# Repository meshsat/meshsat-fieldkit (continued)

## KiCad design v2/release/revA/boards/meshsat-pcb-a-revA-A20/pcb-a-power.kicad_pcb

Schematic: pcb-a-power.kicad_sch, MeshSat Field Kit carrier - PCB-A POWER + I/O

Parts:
C7, C14, C61, C62, C106: 10u; C_0805_2012Metric
C13, C44, C67, C68, C77, C90, C100, C104, C105, C107, C108: 100n; C_0603_1608Metric
C15, C42, C43, C45, C46, C47, C48, C49, C70, C75, C76, C78, C79, C80, C81, C82, C83, C88, C89, C91, C92, C93, C94, C101: 22u 10V X7R 1210; C_1210_3225Metric
C38, C71, C84: 100n 25V; C_0603_1608Metric
C39, C72, C85: 2.2u; C_0603_1608Metric
C40, C73, C86: 3.3n; C_0603_1608Metric
C41, C74, C87: 27p; C_0603_1608Metric
C50, C95, C96, C97: 100u 10V; C_1206_3216Metric
C51, C52, C53, C54, C55, C56, C57, C58, C59, C60: 10u 25V 1210; C_1210_3225Metric
C63, C64: 47n; C_0603_1608Metric
C65: 4.7u; C_0805_2012Metric
C66: 1n; C_0603_1608Metric
C69, C98: 1u; C_0603_1608Metric
C99: 10n; C_0603_1608Metric
D2: SMBJ5.0A; D_SMB
F2, F3, F4: 10 A mini blade (Keystone 3568 holder): pack node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; Fuseholder_Blade_Mini_Keystone_3568
F5: 15 A mini blade (Keystone 3568 holder): pack node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; Fuseholder_Blade_Mini_Keystone_3568
F6: 2.5A hold 30V 1812; Fuse_1812_4532Metric
J_5V_M1: rail M1 to PCB-B J_5V_M1 (JST-VH, 18 AWG): + -; JST_VH_B2P-VH_1x02_P3.96mm_Vertical
J_5V_M2: rail M2 to PCB-B J_5V_M2 (JST-VH, 18 AWG): + -; JST_VH_B2P-VH_1x02_P3.96mm_Vertical
J_5V_PI: Pi rail 5.1 V 5 A to PCB-B J_5V_PI (JST-VH, 18 AW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; JST_VH_B2P-VH_1x02_P3.96mm_Vertical
J_AB1: A-B interconnect (IDC 2x9, top side); IDC-Header_2x09_P2.54mm_Vertical
J_BM1, J_BM2, J_BM3, J_BM4, J_BM5, J_BM6, J_BM7: SMP-MAX slide-on receptacle R222M00720 (underside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; Radiall_SMPMAX_R222M00720
J_CN1, J_CN2, J_CN3, J_CN4: 9 A spring pin, module return CELL_N (Mill-Max 08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; Mill-Max_0858_power_pin
J_CP1, J_CP2, J_CP3, J_CP4: 9 A spring pin, CELL+ (Mill-Max 0858 class, dock 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; Mill-Max_0858_power_pin
J_DOCK: spring pins to the dock block (2x6, Preci-Dip 813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; PogoPins_2x6
J_HEAT: 12 V heating pad on the battery module (XH2.5): +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; JST_XH_B2B-XH-A_1x02_P2.50mm_Vertical
J_LEDS1: front-wall LED row (XH2.5): PWR MESH SAT LTE SYS; JST_XH_B10B-XH-A_1x10_P2.50mm_Vertical
J_MAINSW: MAIN button lead from the panel (XH2.5): PB, GND; JST_XH_B2B-XH-A_1x02_P2.50mm_Vertical
J_MEZZ1: APRS mezzanine harness (IDC 2x8): I2S and I2C for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; IDC-Header_2x08_P2.54mm_Vertical
J_MEZZ_PWR1: mezzanine 8 V boost feed (JST-VH): cell node thro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; JST_VH_B2P-VH_1x02_P3.96mm_Vertical
J_PRE1: pre-charge pin, longer, mates first (32.24 AX); Mill-Max_0858_power_pin
J_RF1, J_RF2, J_RF3, J_RF4, J_RF5, J_RF6, J_RF7: SMA jack (Amphenol 132134, vertical), pigtail fro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; SMA_Amphenol_132134-11_Vertical
J_WALL1: USB-A receptacle, internal cable to the Glenair 2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; USB_A_Stewart_SS-52100-001_Horizontal
L2, L3, L4: 2.2uH XAL1010-222MED (Isat 34 A, 10 mm); L_Coilcraft_XAL1010-XXX
L5: 2.2uH XAL4030-222MEB (Isat 7.4 A) between SW1 and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; L_Coilcraft_XAL4030-XXX
L6: 3.3uH XAL4020-332MEB; L_Coilcraft_XAL4020-XXX
Q5: 2N7002: Pi GPIO high = pull KILL low = power off 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; SOT-23
R18: 1k; R_0603_1608Metric
R34, R59, R60, R72, R76: 10k; R_0603_1608Metric
R35, R36, R37, R38: 330R; R_0603_1608Metric
R39, R58, R67, R68, R69, R70, R73, R77: 100k; R_0603_1608Metric
R44, R61, R64: 8.87k; R_0603_1608Metric
R47, R62: 102k 1%; R_0603_1608Metric
R48, R63: 13.7k 1%; R_0603_1608Metric
R51: 10R 2W 2512; R_2512_6332Metric
R52: 3 mOhm 1% 3 W 2512 shunt (RALEC LR2512-23R003F4):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; R_2512_6332Metric; LCSC C154688
R53: 4.7k 1% (PROG: 1S, 750 kHz); R_0603_1608Metric
R54: 16.5k 1%; R_0603_1608Metric
R55: 34.8k 1%; R_0603_1608Metric
R56: 5.23k 1% (RT1 JEITA); R_0603_1608Metric
R57: 30.1k 1% (RT2 JEITA); R_0603_1608Metric
R65: 75k 1%; R_0603_1608Metric
R66, R75: 10k 1%; R_0603_1608Metric
R71: 1.02k 1% (2.0 A); R_0603_1608Metric
R74: 33.2k 1%; R_0603_1608Metric
R78: 0.1R 1% 1206; R_1206_3216Metric
RT1: 10k NTC 0603 1% (gauge temperature, beside the do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; R_0603_1608Metric
TP1: +5V_M1; TestPoint_Pad_D1.5mm
TP2: GND; TestPoint_Pad_D1.5mm
TP3: +3V3; TestPoint_Pad_D1.5mm
TP4: CELL_N; TestPoint_Pad_D1.5mm
TP5: CELL+; TestPoint_Pad_D1.5mm
TP6: SHORE_INHIBIT; TestPoint_Pad_D1.5mm
TP7: GAUGE_ALERT; TestPoint_Pad_D1.5mm
TP8: I2S_DIN; TestPoint_Pad_D1.5mm
TP9: TX_INHIBIT_n; TestPoint_Pad_D1.5mm
TP10: SHORE_12V; TestPoint_Pad_D1.5mm
TP11: CHG_INT; TestPoint_Pad_D1.5mm
TP12: +5V_M2; TestPoint_Pad_D1.5mm
TP13: +5V_PI; TestPoint_Pad_D1.5mm
TP14: DOCK_SPARE; TestPoint_Pad_D1.5mm
TP15: BOOST_EN; TestPoint_Pad_D1.5mm
TP16: CELL_SENSE_P; TestPoint_Pad_D1.5mm
TP17: EXP_SP2; TestPoint_Pad_D1.5mm
TP18: EXP_SP3; TestPoint_Pad_D1.5mm
TP19: EXP2_SP0; TestPoint_Pad_D1.5mm
TP20: EXP2_SP1; TestPoint_Pad_D1.5mm
TP21: EXP2_SP2; TestPoint_Pad_D1.5mm
TP22: EXP2_SP3; TestPoint_Pad_D1.5mm
TP23: EXP2_SP4; TestPoint_Pad_D1.5mm
TP24: EXP2_SP5; TestPoint_Pad_D1.5mm
TP25: EXP2_SP6; TestPoint_Pad_D1.5mm
TP26: EXP2_SP7; TestPoint_Pad_D1.5mm
TP27: EXP2_SP8; TestPoint_Pad_D1.5mm
TP29: EXP_SP4; TestPoint_Pad_D1.5mm
TP30: EXP_SP5; TestPoint_Pad_D1.5mm
TP31: EXP_SP6; TestPoint_Pad_D1.5mm
TP32: EXP_SP7; TestPoint_Pad_D1.5mm
TP33: EXP_SP8; TestPoint_Pad_D1.5mm
TP34: EXP_SP9; TestPoint_Pad_D1.5mm
TP35: EXP_SP10; TestPoint_Pad_D1.5mm
TP36: EXP_SP11; TestPoint_Pad_D1.5mm
U5: TPS563201 3.3 V buck from M1; SOT-23-6
U19: PCA9555PW (0x21); TSSOP-24_4.4x7.8mm_P0.65mm; LCSC C5626
U20: BQ25792 1S charger from SHORE_12V (3 A set over I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; Texas_RQM0029A_QFN-29_4x4mm; LCSC C2862876
U21: BQ34Z100-G1 gauge (I2C 0x55, SCALED for 42 Ah, 3 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; TSSOP-14_4.4x5mm_P0.65mm; LCSC C91302
U22: TPS61288L boost +5V_M1 (15 A switch, 500 kHz, no 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; Texas_RQQ0011A_VQFN-HR-11_2.5x3mm; LCSC C7498841
U23: TPS61288L boost +5V_M2 (15 A switch, 500 kHz, no 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; Texas_RQQ0011A_VQFN-HR-11_2.5x3mm; LCSC C7498841
U24: TPS61288L boost +5V_PI (15 A switch, 500 kHz, no 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; Texas_RQQ0011A_VQFN-HR-11_2.5x3mm; LCSC C7498841
U25: LTC2954CTS8-1 push-button on/off controller; TSOT-23-8; LCSC C683782
U26: TPS259571DSGR eFuse 12 V 2.0 A for the heating pad; Texas_DSG0008A_WSON-8-1EP_2x2mm_P0.5mm_EP0.9x1.6mm; LCSC C471038
U28: TPS2065CDBV; SOT-23-5
U29: INA219AIDCN; SOT-23-8; LCSC C138024
U30: USBLC6-2SC6; SOT-23-6; LCSC C7519
U31: PCA9555PW (0x24): wall port, heating pad, charger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; TSSOP-24_4.4x7.8mm_P0.65mm; LCSC C5626

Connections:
+3V3: C15.1, C101.1, C105.1, C107.1, C108.1, J_MEZZ1.12, L6.2, R34.2, R35.1, R36.1, R37.1, R38.1, R60.2, R68.2, R72.2, R74.1, R76.2, R77.2, TP3.1, U19.21 (A0), U19.24 (VDD), U29.4 (VS), U31.3 (A2), U31.24 (VDD)
/5V_WALL: C106.1, J_WALL1.1 (VBUS), R78.2, U29.2 (IN-), U30.5 (VBUS)
/+3V3_AB: J_AB1.17, J_MEZZ1.2
/+5V_M1: C14.1, C45.1, C46.1, C47.1, C48.1, C49.1, C70.1, C95.1, C104.1, D2.1 (A1), J_5V_M1.1, R18.1, R47.1, TP1.1, U5.3 (VIN), U5.5 (EN), U22.5, U28.5 (IN)
/+5V_M2: C78.1, C79.1, C80.1, C81.1, C82.1, C83.1, C96.1, J_5V_M2.1, R62.1, TP12.1, U23.5
/+5V_PI: C91.1, C92.1, C93.1, C94.1, C97.1, J_5V_PI.1, R65.1, TP13.1, U24.5
/BOOST1_IN: C42.1, C43.1, C44.1, F3.2, L2.1, U22.7
/BOOST2_IN: C75.1, C76.1, C77.1, F4.2, L3.1, U23.7
/BOOST3_IN: C88.1, C89.1, C90.1, F5.2, L4.1, U24.7
/BOOST_EN: R67.1, TP15.1, U22.6, U23.6, U24.6, U25.6
/BST1: C38.1, U22.8
/BST2: C71.1, U23.8
/BST3: C84.1, U24.8
/BST33: C13.1, U5.6 (VBST)
/BTST1: C63.1, U20.4
/BTST2: C64.1, U20.19
/CELL+: C7.1, C50.1, C61.1, C62.1, C68.1, C98.1, F2.1, F3.1, F4.1, F5.1, J_CP1.1, J_CP2.1, J_CP3.1, J_CP4.1, R51.2, R67.2, R69.2, TP5.1, U20.22, U20.23, U21.5, U21.6, U25.1
/CELL_N: C68.2, C69.2, J_CN1.1, J_CN2.1, J_CN3.1, J_CN4.1, R52.1, TP4.1, U21.8, U21.9
/CELL_SENSE_P: C67.1, J_DOCK.11, TP16.1, U20.18, U21.4
/CHG_INT: R60.1, TP11.1, U20.21, U31.8 (IO0_4)
/CHG_STAT: R59.1, U20.1, U31.10 (IO0_6)
/COMP1: C41.1, R44.1, U22.2
/COMP1C: C40.1, R44.2
/COMP2: C74.1, R61.1, U23.2
/COMP2C: C73.1, R61.2
/COMP3: C87.1, R64.1, U24.2
/COMP3C: C86.1, R64.2
/DOCK_SPARE: J_DOCK.12, TP14.1
/EN_WALL: R77.1, U28.4 (EN), U31.4 (IO0_0)
/EXP2_SP0: TP19.1, U31.11 (IO0_7)
/EXP2_SP1: TP20.1, U31.13 (IO1_0)
/EXP2_SP2: TP21.1, U31.14 (IO1_1)
/EXP2_SP3: TP22.1, U31.15 (IO1_2)
/EXP2_SP4: TP23.1, U31.16 (IO1_3)
/EXP2_SP5: TP24.1, U31.17 (IO1_4)
/EXP2_SP6: TP25.1, U31.18 (IO1_5)
/EXP2_SP7: TP26.1, U31.19 (IO1_6)
/EXP2_SP8: TP27.1, U31.20 (IO1_7)
/EXP_INT: J_AB1.9, R34.1, U19.1 (~INT), U31.1 (~INT)
/EXP_SP2: TP17.1, U19.9 (IO0_5)
/EXP_SP3: TP18.1, U19.20 (IO1_7)
/EXP_SP4: TP29.1, U19.4 (IO0_0)
/EXP_SP5: TP30.1, U19.5 (IO0_1)
/EXP_SP6: TP31.1, U19.6 (IO0_2)
/EXP_SP7: TP32.1, U19.7 (IO0_3)
/EXP_SP8: TP33.1, U19.16 (IO1_3)
/EXP_SP9: TP34.1, U19.17 (IO1_4)
/EXP_SP10: TP35.1, U19.18 (IO1_5)
/EXP_SP11: TP36.1, U19.19 (IO1_6)
/FB1: R47.2, R48.1, U22.1
/FB2: R62.2, R63.1, U23.1
/FB3: R65.2, R66.1, U24.1
/FB33: R74.2, R75.1, U5.4 (VFB)
/FLT_WALL: R76.1, U28.3 (~FLT), U31.6 (IO0_2)
/GAUGE_ALERT: TP7.1, U21.1, U31.9 (IO0_5)
/HEAT_DVDT: C99.1, U26.1
/HEAT_EN: R73.1, U26.2, U31.5 (IO0_1)
/HEAT_FLT: R72.1, U26.6, U31.7 (IO0_3)
/HEAT_ILM: R71.1, U26.7
/HEAT_IN: C100.1, F6.2, U26.3, U26.4
/HEAT_OUT: J_HEAT.1, U26.5
/I2S_BCLK: J_AB1.11, J_MEZZ1.3
/I2S_DIN: J_AB1.16, J_MEZZ1.7, TP8.1
/I2S_DOUT: J_AB1.15, J_MEZZ1.6
/I2S_LRCLK: J_AB1.12, J_MEZZ1.4
/ILIM_HIZ: R54.2, R55.1, U20.17
/KILL: Q5.3 (D), R69.1, U25.8
/LED_LTE_A: J_LEDS1.7, R37.2
/LED_LTE_K: J_LEDS1.8, U19.14 (IO1_1)
/LED_MESH_A: J_LEDS1.3, R35.2
/LED_MESH_K: J_LEDS1.4, U19.11 (IO0_7)
/LED_PWR_A: J_LEDS1.1, R18.2
/LED_SAT_A: J_LEDS1.5, R36.2
/LED_SAT_K: J_LEDS1.6, U19.13 (IO1_0)
/LED_SYS_A: J_LEDS1.9, R38.2
/LED_SYS_K: J_LEDS1.10, U19.15 (IO1_2)
/MAIN_PB: J_MAINSW.1, U25.2
/MEZZ_CELL: F2.2, J_MEZZ_PWR1.1
/MEZZ_EN: J_MEZZ1.11, U19.10 (IO0_6)
/PI_KILL: J_AB1.2, Q5.1 (G), R70.1
/PI_SHDN_REQ: J_AB1.1, R68.1, U25.5
/PMID: C53.1, C54.1, C55.1, U20.29
/PRECHG: J_PRE1.1, R51.1
/PROG: R53.1, U20.20
/QON: R58.2, U20.12
/REG25: C69.1, RT1.1, U21.7
/REGN: C65.1, R54.1, R56.1, R58.1, R59.2, U20.5
/RF_IRIDIUM: J_BM6.1 (In), J_RF6.1 (In)
/RF_LORA: J_BM7.1 (In), J_RF7.1 (In)
/RF_LTE: J_BM5.1 (In), J_RF5.1 (In)
/RF_SDR: J_BM4.1 (In), J_RF4.1 (In)
/RF_UHF: J_BM1.1 (In), J_RF1.1 (In)
/RF_WIFI24: J_BM2.1 (In), J_RF2.1 (In)
/RF_WIFI58: J_BM3.1 (In), J_RF3.1 (In)
/SCL: J_AB1.8, J_MEZZ1.14, U19.22 (SCL), U20.14, U21.13, U29.5 (SCL), U31.22 (SCL)
/SDA: J_AB1.7, J_MEZZ1.9, U19.23 (SDA), U20.15, U21.14, U29.6 (SDA), U29.7 (A0), U29.8 (A1), U31.23 (SDA)
/SDRV: C66.1, U20.24
/SHORE_12V: C51.1, C52.1, F6.1, J_DOCK.1, J_DOCK.2, J_DOCK.3, J_DOCK.4, TP10.1, U20.2, U20.3, U20.8, U20.9
/SHORE_INHIBIT: J_DOCK.8, TP6.1, U19.8 (IO0_4)
/SW1: C38.2, L2.2, U22.4, U22.9
/SW1_CHG: C63.2, L5.1, U20.28
/SW2: C71.2, L3.2, U23.4, U23.9
/SW2_CHG: C64.2, L5.2, U20.26
/SW3: C84.2, L4.2, U24.4, U24.9
/SW33: C13.2, L6.1, U5.2 (SW)
/SW_WALL: R78.1, U28.1 (OUT), U29.1 (IN+)
/SYS_CHG: C56.1, C57.1, C58.1, C59.1, C60.1, U20.25
/TR_APRS: J_AB1.10, J_MEZZ1.10, R39.1
/TS_CHG: J_DOCK.9, R56.2, R57.1, U20.16
/TS_GAUGE: RT1.2, U21.11
/TX_INHIBIT_n: J_AB1.14, J_MEZZ1.15, TP9.1
/USB_WALL_N: J_AB1.5, J_WALL1.2 (D-), U30.3 (I/O2), U30.4 (I/O2)
/USB_WALL_P: J_AB1.4, J_WALL1.3 (D+), U30.1 (I/O1), U30.6 (I/O1)
/VCC1: C39.1, U22.11
/VCC2: C72.1, U23.11
/VCC3: C85.1, U24.11
GND: C7.2, C14.2, C15.2, C39.2, C40.2, C41.2, C42.2, C43.2, C44.2, C45.2, C46.2, C47.2, C48.2, C49.2, C50.2, C51.2, C52.2, C53.2, C54.2, C55.2, C56.2, C57.2, C58.2, C59.2, C60.2, C61.2, C62.2, C65.2, C66.2, C67.2, C70.2, C72.2, C73.2, C74.2, C75.2, C76.2, C77.2, C78.2, C79.2, C80.2, C81.2, C82.2, C83.2, C85.2, C86.2, C87.2, C88.2, C89.2, C90.2, C91.2, C92.2, C93.2, C94.2, C95.2, C96.2, C97.2, C98.2, C99.2, C100.2, C101.2, C104.2, C105.2, C106.2, C107.2, C108.2, D2.2 (A2), J_5V_M1.2, J_5V_M2.2, J_5V_PI.2, J_AB1.3, J_AB1.6, J_AB1.13, J_AB1.18, J_BM1.2 (Ext), J_BM2.2 (Ext), J_BM3.2 (Ext), J_BM4.2 (Ext), J_BM5.2 (Ext), J_BM6.2 (Ext), J_BM7.2 (Ext), J_DOCK.5, J_DOCK.6, J_DOCK.7, J_DOCK.10, J_HEAT.2, J_LEDS1.2, J_MAINSW.2, J_MEZZ1.1, J_MEZZ1.5, J_MEZZ1.8, J_MEZZ1.13, J_MEZZ1.16, J_MEZZ_PWR1.2, J_RF1.2 (Ext), J_RF2.2 (Ext), J_RF3.2 (Ext), J_RF4.2 (Ext), J_RF5.2 (Ext), J_RF6.2 (Ext), J_RF7.2 (Ext), J_WALL1.4 (GND), J_WALL1.5 (Shield), Q5.2 (S), R39.2, R48.2, R52.2, R53.2, R55.2, R57.2, R63.2, R66.2, R70.2, R71.2, R73.2, R75.2, TP2.1, U5.1 (GND), U19.2 (A1), U19.3 (A2), U19.12 (VSS), U20.10, U20.11, U20.13, U20.27, U21.10, U22.3, U22.10, U23.3, U23.10, U24.3, U24.10, U25.4, U26.8, U26.9, U28.2 (GND), U29.3 (GND), U30.2 (GND), U31.2 (A1), U31.12 (VSS), U31.21 (A0)

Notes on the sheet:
PACK NODE (A19): MODULE CURRENT OVER THE DOCK PINS, PRE-CHARGE, GAUGE SHUNT, MEZZANINE FEED
CHARGER BQ25792 (SHORE_12V -> CELL+, 3 A, JEITA ON THE MODULE THERMISTOR) + DOCK SIGNAL PINS
GAUGE BQ34Z100-G1 (0x55)
RAIL M1: F3 + TPS61288L 5.05 V (LOGIC, HUB, PCB-B M1)
RAIL M2: F4 + TPS61288L 5.05 V (PCB-B M2)
RAIL PI: F5 + TPS61288L 5.1 V 5 A
MAIN POWER CONTROL LTC2954 + HEATING PAD SWITCH TPS259571
3.3 V BUCK TPS563201 FROM M1, TEST POINTS, FLAGS
CH5 WALL HOST PORT (0x4A)
I2C EXPANDERS PCA9555 0x21 AND 0x24, LEDs
MEZZANINE HARNESS + A-B INTERCONNECT 2x9 (A20)
SEVEN BLIND-MATE RF SITES: SMA JACK (TOP) + SMP-MAX RECEPTACLE (UNDERSIDE)

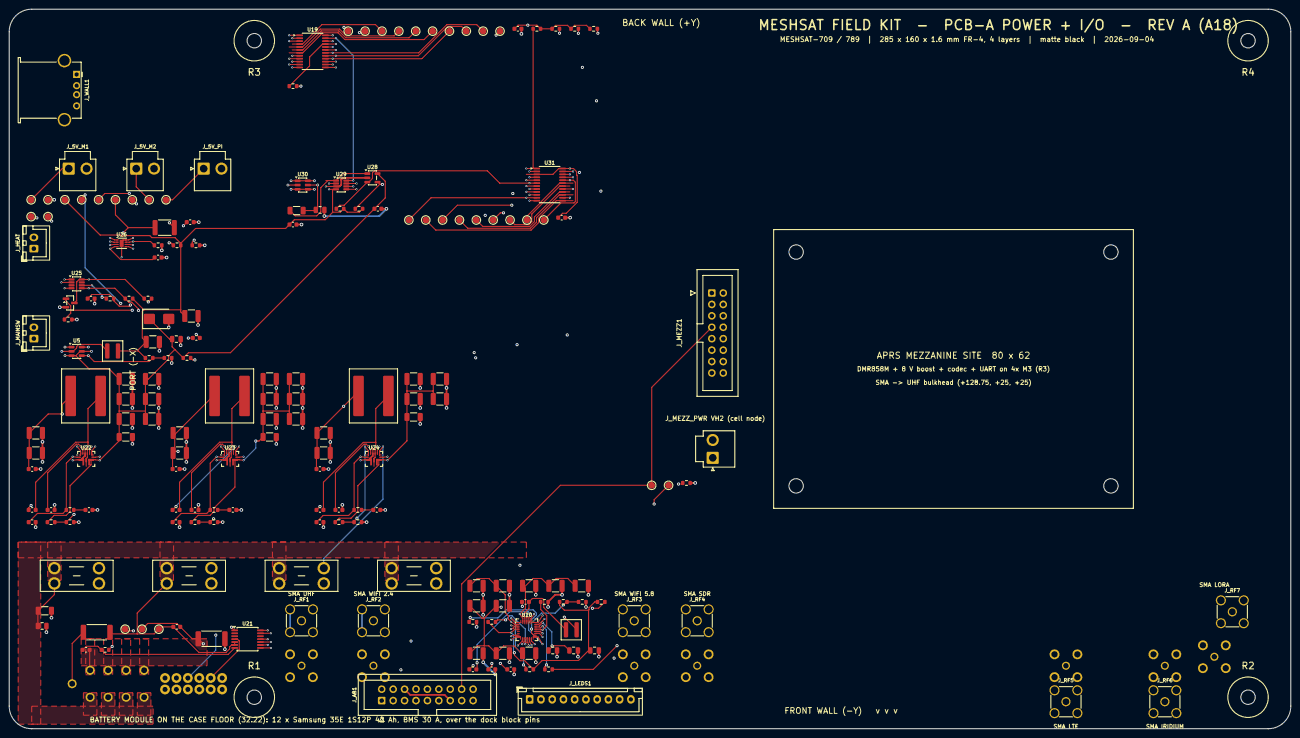
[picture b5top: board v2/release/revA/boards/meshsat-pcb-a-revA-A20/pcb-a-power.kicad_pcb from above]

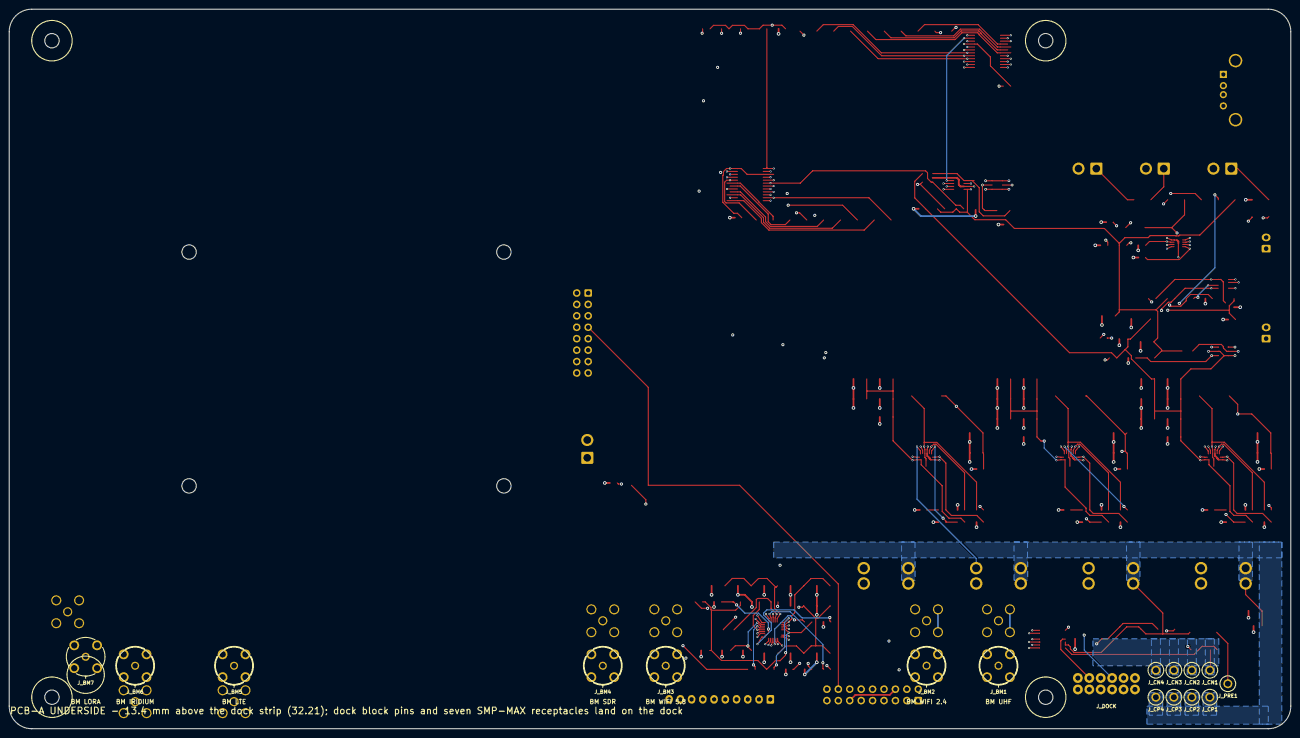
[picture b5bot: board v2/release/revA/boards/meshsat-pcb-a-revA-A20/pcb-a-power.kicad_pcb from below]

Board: 4 copper layers, 285.0 x 160.0 mm, 214 parts (17 on the bottom side), 117 nets.

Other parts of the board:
H1: M3 rod R1; MountingHole_3.2mm_M3
H2: M3 rod R2; MountingHole_3.2mm_M3
H3: M3 rod R3; MountingHole_3.2mm_M3
H4: M3 rod R4; MountingHole_3.2mm_M3
H5, H6, H7, H8: M3 standoff, mezzanine; MountingHole_3.2mm_M3
